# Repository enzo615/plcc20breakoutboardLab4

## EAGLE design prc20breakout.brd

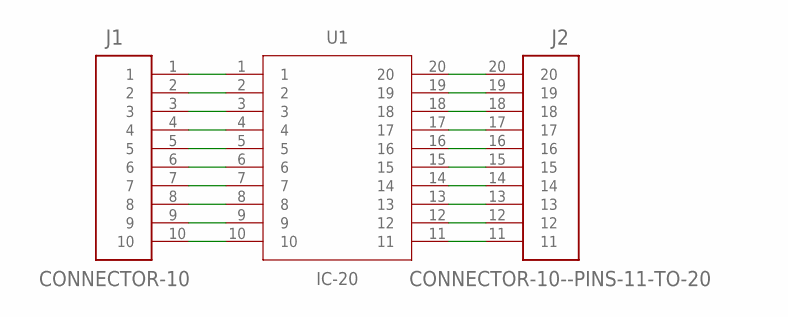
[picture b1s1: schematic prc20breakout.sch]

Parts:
J1: CONNECTOR-10; ESQ-110-XX-XX-S
J2: CONNECTOR-10--PINS-11-TO-20; ESQ-110-XX-XX-S--ROUND-PIN-1
U1: IC-20; PLCC127P990X990X457-20N

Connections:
unnamed: J1.4, U1.4
unnamed: J1.1, U1.1
unnamed: J1.5, U1.5
unnamed: J1.2, U1.2
unnamed: J1.6, U1.6
unnamed: J1.3, U1.3
unnamed: J1.7, U1.7
unnamed: J1.8, U1.8
unnamed: J1.9, U1.9
unnamed: J1.10, U1.10
unnamed: J2.14, U1.14
unnamed: J2.11, U1.11
unnamed: J2.15, U1.15
unnamed: J2.12, U1.12
unnamed: J2.16, U1.16
unnamed: J2.13, U1.13
unnamed: J2.17, U1.17
unnamed: J2.18, U1.18
unnamed: J2.19, U1.19
unnamed: J2.20, U1.20

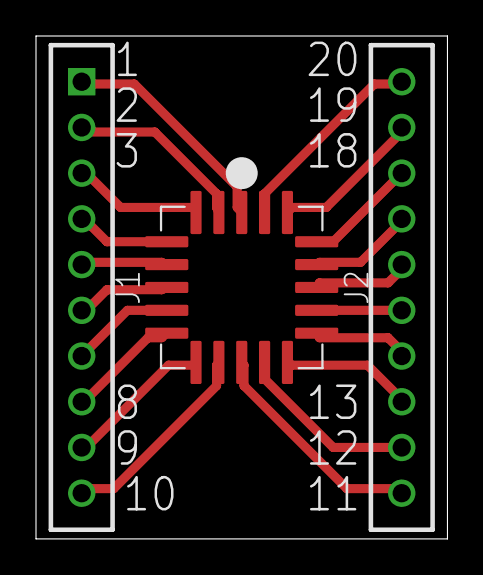
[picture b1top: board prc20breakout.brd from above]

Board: 2 copper layers, 22.9 x 27.9 mm, 3 parts (0 on the bottom side), 20 nets.

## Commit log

2022-02-06 Add files via upload
    lab 4 breakout board and stuff, also ignore the fact that it says "prc20" instead of "plcc20" i was trying to put the letters from memory and my memory clearly failed me
